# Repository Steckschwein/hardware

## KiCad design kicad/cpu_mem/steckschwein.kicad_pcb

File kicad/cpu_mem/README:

OBSOLETE

This is the old CPU/memory board without RDY-generator.
It has been superseded by ../cpu_mem_rdy

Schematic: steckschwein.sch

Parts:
C1, C5, C6, C7, C8, C9, C10: 100n; C1
C2: 10n; C1
C3: 1n; C1
C4: 1µ; Elko_vert_DM5_RM2-5
C16: CP2; Elko_vert_11.2x7.5mm_RM2.5
D1, D2, D3: LED; LED-3MM
P1: CONN_02X04; Pin_Header_Straight_2x04
P3: CONN_01X03; Pin_Header_Straight_1x03
P4: CONN_02X02; Pin_Header_Straight_2x02
P6: POWER; Pin_Header_Angled_1x04
R1, R2, R3, R4: 3.3k; R3
R5, R6: 1M; R3
R7, R8, R9: 270; R3
SW1: SW_PUSH; PUSH_BUTT_SHAPE1
U1: W65C02SP; DIP-40__600_ELL
U2: LM555N; DIP-8__300_ELL
U3: 74HCT00; DIP-14__300_ELL
U4: 74LS393; DIP-14__300_ELL
U6: 28C256; DIP-28__600_ELL
U7, U8: HM62256BLP-7; DIP-28__600_ELL
X1: OSC; OSCILLATOR_KXO-200_LargePads

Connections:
/Connector/A0: U1.9 (A0), U6.10 (A0), U7.10 (A0), U8.10 (A0); also elsewhere on the board
/Connector/A1: U1.10 (A1), U6.9 (A1), U7.9 (A1), U8.9 (A1); also elsewhere on the board
/Connector/A2: U1.11 (A2), U6.8 (A2), U7.8 (A2), U8.8 (A2); also elsewhere on the board
/Connector/A3: U1.12 (A3), U6.7 (A3), U7.7 (A3), U8.7 (A3); also elsewhere on the board
/Connector/A4: U1.13 (A4), U6.6 (A4), U7.6 (A4), U8.6 (A4); also elsewhere on the board
/Connector/A5: U1.14 (A5), U6.5 (A5), U7.5 (A5), U8.5 (A5); also elsewhere on the board
/Connector/D0: U1.33 (D0), U6.11 (D0), U7.11 (D0), U8.11 (D0); also elsewhere on the board
/Connector/D1: U1.32 (D1), U6.12 (D1), U7.12 (D1), U8.12 (D1); also elsewhere on the board
/Connector/D2: U1.31 (D2), U6.13 (D2), U7.13 (D2), U8.13 (D2); also elsewhere on the board
/Connector/D3: U1.30 (D3), U6.15 (D3), U7.15 (D3), U8.15 (D3); also elsewhere on the board
/Connector/D4: U1.29 (D4), U6.16 (D4), U7.16 (D4), U8.16 (D4); also elsewhere on the board
/Connector/D5: U1.28 (D5), U6.17 (D5), U7.17 (D5), U8.17 (D5); also elsewhere on the board
/Connector/D6: U1.27 (D6), U6.18 (D6), U7.18 (D6), U8.18 (D6); also elsewhere on the board
/Connector/D7: U1.26 (D7), U6.19 (D7), U7.19 (D7), U8.19 (D7); also elsewhere on the board
/Connector/RESET_TRIG: C2.1, R5.2, SW1.1, U2.2 (TR); also elsewhere on the board
/IRQ: R1.1, U1.4 (IRQB); also elsewhere on the board
/NMI: R2.1, U1.6 (NMIB); also elsewhere on the board
/OE: U3.6, U6.22 (OE), U7.22 (~OE), U8.22 (~OE); also elsewhere on the board
/RESET: U1.40 (RESB), U3.11; also elsewhere on the board
/RW: U1.34 (R/WB), U3.1, U3.2, U3.4; also elsewhere on the board
/WE: U3.8, U7.27 (~WE), U8.27 (~WE); also elsewhere on the board
/decoder//CS_HIRAM: D3.2, U8.20 (~CS); also elsewhere on the board
/decoder//CS_LORAM: D2.2, U7.20 (~CS); also elsewhere on the board
/decoder//CS_ROM: D1.2, U6.20 (CS); also elsewhere on the board
/decoder/A6: U1.15 (A6), U6.4 (A6), U7.4 (A6), U8.4 (A6); also elsewhere on the board
/decoder/A7: U1.16 (A7), U6.3 (A7), U7.3 (A7), U8.3 (A7); also elsewhere on the board
/decoder/A8: U1.17 (A8), U6.25 (A8), U7.25 (A8), U8.25 (A8); also elsewhere on the board
/decoder/A9: U1.18 (A9), U6.24 (A9), U7.24 (A9), U8.24 (A9); also elsewhere on the board
/decoder/A10: U1.19 (A10), U6.21 (A10), U7.21 (A10), U8.21 (A10); also elsewhere on the board
/decoder/A11: U1.20 (A11), U6.23 (A11), U7.23 (A11), U8.23 (A11); also elsewhere on the board
/decoder/A12: U1.22 (A12), U6.2 (A12), U7.2 (A12), U8.2 (A12); also elsewhere on the board
/decoder/A13: U1.23 (A13), U7.26 (A13), U8.26 (A13); also elsewhere on the board
/decoder/A14: U1.24 (A14), U7.1 (A14), U8.1 (A14); also elsewhere on the board
/decoder/A15: U1.25 (A15); also elsewhere on the board
/decoder/BANK1: U6.26 (A13); also elsewhere on the board
/decoder/BANK2: U6.1 (A14); also elsewhere on the board
GND: C1.2, C2.2, C3.2, C4.2, C5.2, C6.2, C7.2, C8.2, C9.2, C10.2, C16.2, P4.4, P6.2, P6.3, SW1.2, U1.21 (VSS), U2.1 (GND), U3.7 (GND), U4.2 (Mr), U4.7 (GND), U4.12 (Mr), U4.13 (Cp), U6.14 (GND), U7.14 (GND), U8.14 (GND), X1.7 (GND); also elsewhere on the board
unnamed: C3.1, U2.5 (CV)
unnamed: C4.1, R6.1, U2.6 (THR), U2.7 (DIS)
unnamed: D1.1, R7.1
unnamed: D2.1, R8.1
unnamed: D3.1, R9.1
unnamed: P1.1, P1.3, P1.5, P1.7, P3.1, U1.37 (PH0-IN)
unnamed: P1.2, U4.3 (Q0)
unnamed: P1.4, U4.4 (Q1)
unnamed: P1.6, U4.5 (Q2)
unnamed: P1.8, U4.6 (Q3)
unnamed: P3.3, U1.39 (PHI2)
unnamed: P4.1, U1.36 (BE)
unnamed: P4.2, R4.2
unnamed: P4.3, U1.1 (VPB)
unnamed: U2.3 (Q), U3.12, U3.13
unnamed: U3.3, U3.10
unnamed: U4.1 (Cp), X1.8 (FREQ)
PHI2: P3.2, U3.5, U3.9; also elsewhere on the board
RDY: R3.1, U1.2 (RDY); also elsewhere on the board
VCC: C1.1, C5.1, C6.1, C7.1, C8.1, C9.1, C10.1, C16.1, P6.1, R1.2, R2.2, R3.2, R4.1, R5.1, R6.2, R7.2, R8.2, R9.2, U1.8 (VDD), U2.4 (R), U2.8 (VCC), U3.14 (VCC), U4.14 (VCC), U6.27 (WE), U6.28 (VCC), U7.28 (VCC), U8.28 (VCC), X1.14 (+5V); also elsewhere on the board

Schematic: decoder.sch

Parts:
C11, C12, C13: 100n; C1
D4, D5, D6, D7, D8, D9, D10, D11: LED; LED-3MM
P2: CONN_01X08; Pin_Header_Straight_1x08
R10, R11, R12, R13, R14, R15, R16, R17: 270; R3
U5: GAL22V10; DIP-24__300_ELL
U9: 74LS139; DIP-16__300_ELL
U11: 74LS273; DIP-20__300_ELL
U12: 74LS244; DIP-20__300_ELL

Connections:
/CS_IO0: U9.4 (O0); also elsewhere on the board
/CS_IO1: U9.5 (O1); also elsewhere on the board
/CS_IO2: U9.6 (O2); also elsewhere on the board
/CS_UART: U5.19 (I/O/Q); also elsewhere on the board
/CS_VDP: U5.21 (I/O/Q); also elsewhere on the board
/CS_VIA: U5.20 (I/O/Q); also elsewhere on the board
/Connector/A4: U5.13 (I), U9.2 (A0); also elsewhere on the board
/Connector/A5: U5.11 (I), U9.3 (A1); also elsewhere on the board
/Connector/D0: U11.3, U12.18; also elsewhere on the board
/Connector/D1: U11.4, U12.16; also elsewhere on the board
/Connector/D2: U11.7, U12.14; also elsewhere on the board
/Connector/D3: U11.8, U12.12; also elsewhere on the board
/Connector/D4: U11.13, U12.9; also elsewhere on the board
/Connector/D5: U11.14, U12.7; also elsewhere on the board
/Connector/D6: U11.17, U12.5; also elsewhere on the board
/Connector/D7: U11.18, U12.3; also elsewhere on the board
/RESET: U11.1; also elsewhere on the board
/RW: U5.14 (I/O/Q), U9.14 (A0); also elsewhere on the board
/decoder//CS_HIRAM: U5.18 (I/O/Q); also elsewhere on the board
/decoder//CS_LORAM: U5.17 (I/O/Q); also elsewhere on the board
/decoder//CS_ROM: U5.16 (I/O/Q); also elsewhere on the board
/decoder//ROMOFF: P2.1, R10.2, U5.15 (I/O/Q), U11.2, U12.2
/decoder/A6: U5.10 (I); also elsewhere on the board
/decoder/A7: U5.9 (I); also elsewhere on the board
/decoder/A8: U5.8 (I); also elsewhere on the board
/decoder/A9: U5.7 (I); also elsewhere on the board
/decoder/A10: U5.6 (I); also elsewhere on the board
/decoder/A11: U5.5 (I); also elsewhere on the board
/decoder/A12: U5.4 (I); also elsewhere on the board
/decoder/A13: U5.3 (I); also elsewhere on the board
/decoder/A14: U5.2 (I); also elsewhere on the board
/decoder/A15: U5.1 (I/CLK); also elsewhere on the board
/decoder/BANK1: P2.2, R11.2, U11.5, U12.4; also elsewhere on the board
/decoder/BANK2: P2.3, R12.2, U11.6, U12.6; also elsewhere on the board
GND: C11.2, C12.2, C13.2, D4.2, D5.2, D6.2, D7.2, D8.2, D9.2, D10.2, D11.2, U5.12 (GND), U9.8 (GND), U11.10, U12.10; also elsewhere on the board
unnamed: D4.1, R10.1
unnamed: D5.1, R11.1
unnamed: D6.1, R12.1
unnamed: D7.1, R13.1
unnamed: D8.1, R14.1
unnamed: D9.1, R15.1
unnamed: D10.1, R16.1
unnamed: D11.1, R17.1
unnamed: P2.4, R13.2, U11.9, U12.8
unnamed: P2.5, R14.2, U11.12, U12.11
unnamed: P2.6, R15.2, U11.15, U12.13
unnamed: P2.7, R16.2, U11.16, U12.15
unnamed: P2.8, R17.2, U11.19, U12.17
unnamed: U5.22 (I/O/Q), U9.15 (E)
unnamed: U5.23 (I/O/Q), U9.1 (E)
unnamed: U9.12 (O0), U11.11
unnamed: U9.9 (O3), U12.1, U12.19
PHI2: U9.13 (A1); also elsewhere on the board
VCC: C11.1, C12.1, C13.1, U5.24 (VCC), U9.16 (VCC), U11.20, U12.20; also elsewhere on the board

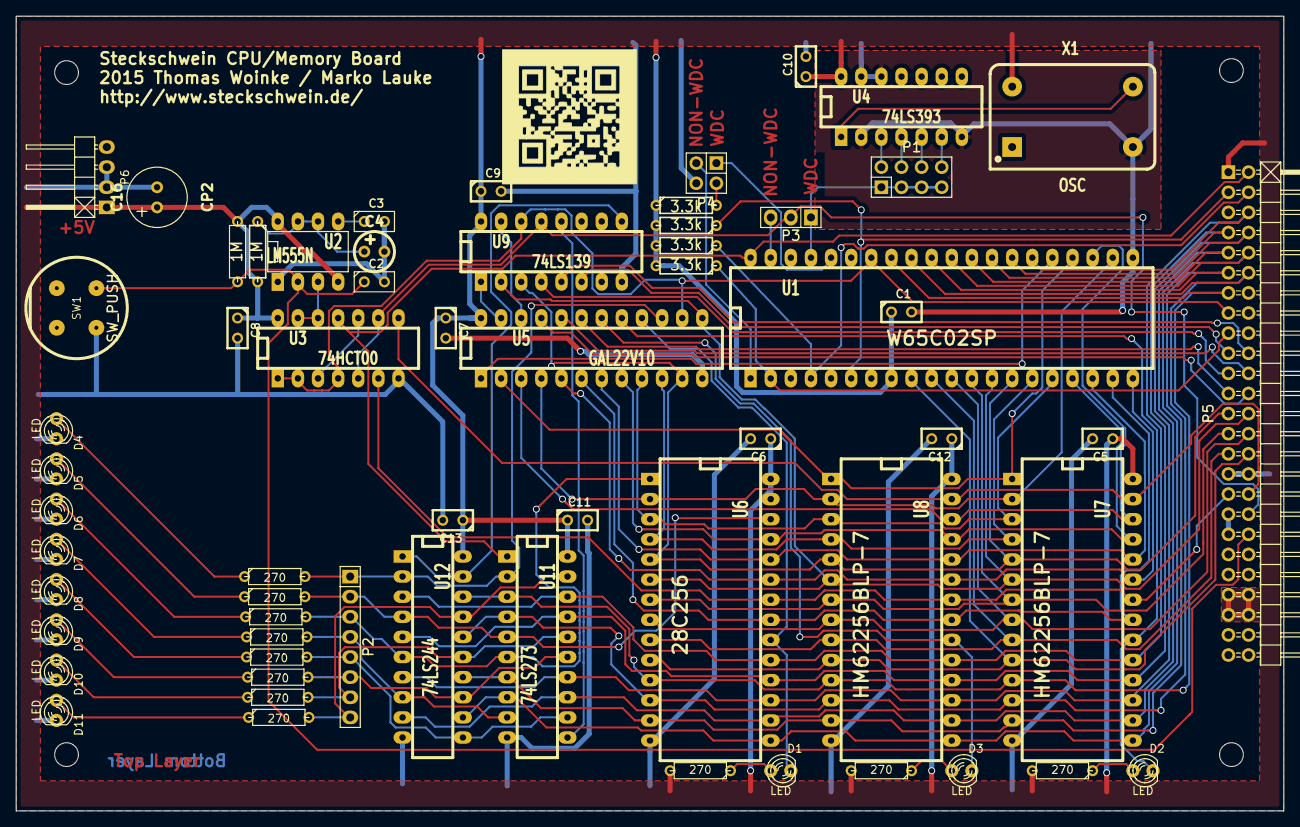
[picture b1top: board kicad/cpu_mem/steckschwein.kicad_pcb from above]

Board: 2 copper layers, 160.0 x 100.3 mm, 65 parts (0 on the bottom side), 81 nets.

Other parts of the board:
MH1, MH2, MH3, MH4: MountingHole_3mm_RevA_Date21Jun2010; MountingHole_3mm
P5: CONN_02X25; Pin_Header_Angled_2x25

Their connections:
/CS_IO0: P5.21; also elsewhere on the board
/CS_IO1: P5.20; also elsewhere on the board
/CS_IO2: P5.19; also elsewhere on the board
/CS_UART: P5.23; also elsewhere on the board
/CS_VDP: P5.24; also elsewhere on the board
/CS_VIA: P5.22; also elsewhere on the board
/Connector/A0: P5.30; also elsewhere on the board
/Connector/A1: P5.29; also elsewhere on the board
/Connector/A2: P5.28; also elsewhere on the board
/Connector/A3: P5.27; also elsewhere on the board
/Connector/A4: P5.26; also elsewhere on the board
/Connector/A5: P5.25; also elsewhere on the board
/Connector/D0: P5.13; also elsewhere on the board
/Connector/D1: P5.12; also elsewhere on the board
/Connector/D2: P5.11; also elsewhere on the board
/Connector/D3: P5.10; also elsewhere on the board
/Connector/D4: P5.9; also elsewhere on the board
/Connector/D5: P5.8; also elsewhere on the board
/Connector/D6: P5.7; also elsewhere on the board
/Connector/D7: P5.6; also elsewhere on the board
/Connector/RESET_TRIG: P5.38; also elsewhere on the board
/IRQ: P5.4; also elsewhere on the board
/NMI: P5.3; also elsewhere on the board
/OE: P5.33; also elsewhere on the board
/RESET: P5.2; also elsewhere on the board
/RW: P5.15; also elsewhere on the board
/WE: P5.34; also elsewhere on the board
GND: P5.31, P5.32, P5.35, P5.37, P5.47, P5.48, P5.49, P5.50; also elsewhere on the board
PHI2: P5.36; also elsewhere on the board
RDY: P5.17; also elsewhere on the board
VCC: P5.1, P5.43, P5.44, P5.45, P5.46; also elsewhere on the board

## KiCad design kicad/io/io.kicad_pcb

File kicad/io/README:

OBSOLETE

This is the old I/O-board without integrated UART.
It has been superseded by ../io_uart

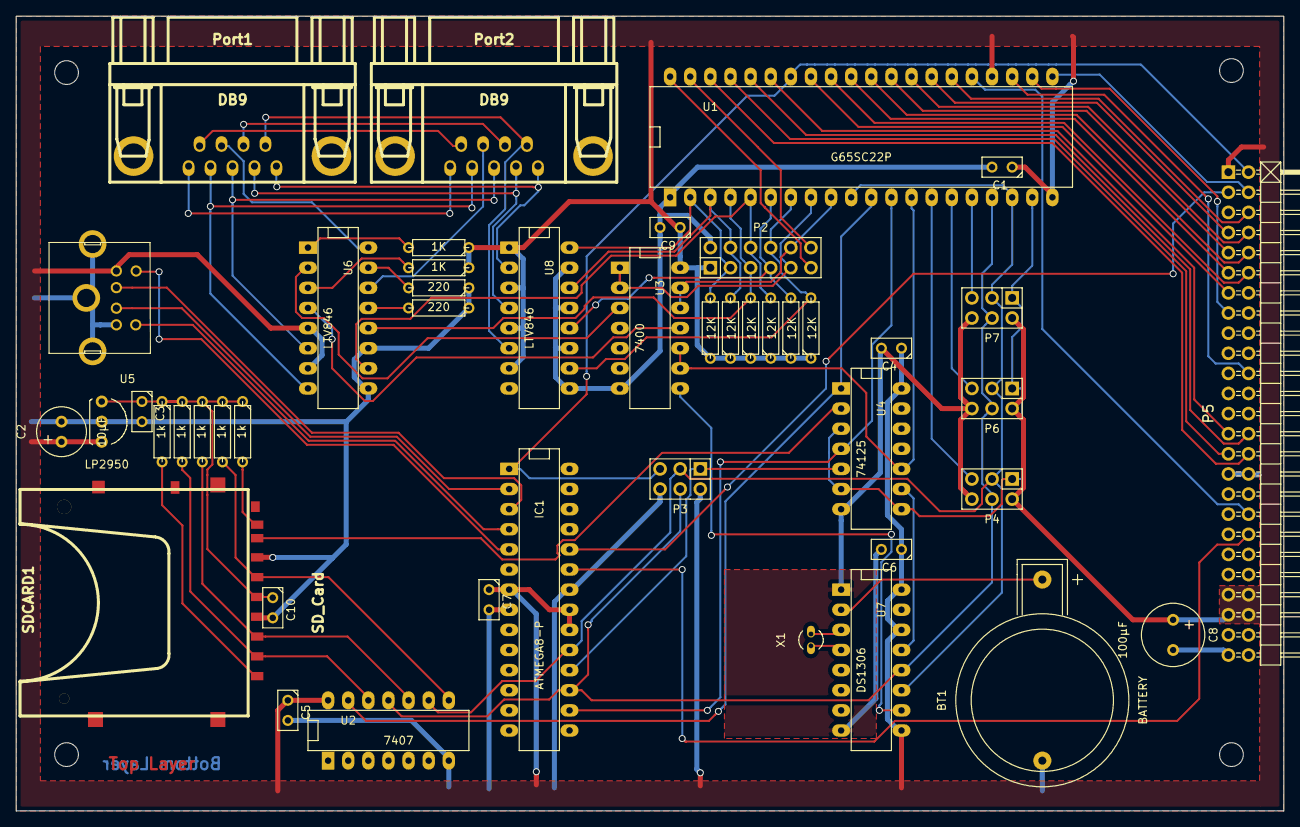
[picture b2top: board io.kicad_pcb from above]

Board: 2 copper layers, 160.0 x 100.3 mm, 50 parts (0 on the bottom side), 73 nets.

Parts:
BT1: BATTERY; CR2032H
C1, C3, C4, C5, C6, C7, C9, C10: 100nF; C1
C2: 10µF; Elko_vert_11.2x6.3mm_RM2.5
C8: 100µF; Elko_vert_11.5x8mm_RM3.5
IC1: ATMEGA8-P; DIP-28__300_ELL
MH1, MH2, MH3, MH4: MountingHole_3mm_RevA_Date21Jun2010; MountingHole_3mm
P1: PS/2 Keyboard; mini_din-M_DIN6
P2: CONN_02X06; Pin_Header_Straight_2x06
P3: ISP; Pin_Header_Straight_2x03
P4: SPI4; Pin_Header_Straight_2x03
P5: CONN_02X25; Pin_Header_Angled_2x25
P6: SPI5; Pin_Header_Straight_2x03
P7: SPI6; Pin_Header_Straight_2x03
Port1, Port2: DB9; DB_9M
R1, R2, R3, R4, R5: 1k; R3
R7, R8, R9, R10, R11, R12: 12K; R3
R13, R14: 220; R3
R15, R16: 1K; R3
SDCARD1: SD_Card; sd_socket
U1: G65SC22P; DIP-40__600_ELL
U2: 7407; DIP-14__300_ELL
U3: 7400; DIP-14__300_ELL
U4: 74125; DIP-14__300_ELL
U5: LP2950; TO-92-Free-inline-wide
U6, U8: LTV846; DIP-16__300_ELL
U7: DS1306; DIP-16__300_ELL
X1: CRYSTAL_SMD; Crystal_Round_Vertical_3mm_BigPad

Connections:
/CA1: P2.11, U1.40
/CA2: P2.12, U1.39
/CS_VIA: P5.22, U1.23
/Connector/A0: P5.30, U1.38
/Connector/A1: P5.29, U1.37
/Connector/A2: P5.28, U1.36
/Connector/A3: P5.27, U1.35
/Connector/D0: P5.13, U1.33
/Connector/D1: P5.12, U1.32
/Connector/D2: P5.11, U1.31
/Connector/D3: P5.10, U1.30
/Connector/D4: P5.9, U1.29
/Connector/D5: P5.8, U1.28
/Connector/D6: P5.7, U1.27
/Connector/D7: P5.6, U1.26
/Connector/RESET_TRIG: IC1.23, P5.38
/IRQ: P5.4, U1.21
/Joystick Ports/J_Down: P2.4, R9.2, U1.3, U8.14
/Joystick Ports/J_Fire1: P2.7, R8.2, U1.6, U8.12
/Joystick Ports/J_Fire2: P2.8, R7.2, U1.7, U8.10
/Joystick Ports/J_Left: P2.5, R12.2, U1.4, U6.12
/Joystick Ports/J_Right: P2.6, R11.2, U1.5, U6.10
/Joystick Ports/J_Up: P2.3, R10.2, U1.2, U8.16
/Joystick Ports/PortSel01: P2.9, U1.8, U3.1, U3.2
/Joystick Ports/PortSel02: P2.10, U1.9, U3.12, U3.13
/NMI: IC1.24, P5.3
/RESET: IC1.1, P3.5, P5.2, U1.34
/RW: P5.15, U1.22
/SD Card/SPI_CLK: IC1.19, P3.3, P4.3, P6.3, P7.3, U1.10, U1.18, U2.9, U7.11
/SD Card/SPI_MISO: P4.1, P6.1, P7.1, U1.19, U4.3, U4.6, U4.8
/SD Card/SPI_MOSI: IC1.17, P3.4, P4.4, P6.4, P7.4, U1.17, U2.11, U7.12
/SD Card/SPI_SS1: U1.11, U2.13, U4.1
/~SPI_SS2: IC1.16, U1.12, U4.4
/~SPI_SS3: U1.13, U3.9, U3.10, U4.10
/~SPI_SS4: P4.5, U1.14
/~SPI_SS5: P6.5, U1.15
/~SPI_SS6: P7.5, U1.16
GND: BT1.2, C1.2, C2.2, C3.2, C4.2, C5.2, C6.2, C7.2, C8.2, C9.2, C10.2, IC1.8, IC1.22, P1.3, P1.SH1, P1.SH2, P1.SH3, P2.2, P3.6, P4.6, P5.31, P5.32, P5.35, P5.37, P5.47, P5.48, P5.49, P5.50, P6.6, P7.6, R13.1, R14.1, SDCARD1.3, SDCARD1.6, U1.1, U2.7, U3.7, U4.7, U5.2, U6.9, U6.11, U7.1, U7.8, U8.9, U8.11, U8.13, U8.15
unnamed: BT1.1, U7.2
unnamed: C3.1, C10.1, R1.1, R2.1, R3.1, R4.1, R5.1, SDCARD1.4, U5.1
unnamed: IC1.2, P1.1
unnamed: IC1.3, P1.2
unnamed: IC1.4, P1.6
unnamed: IC1.5, P1.8
unnamed: IC1.18, P3.1, U4.5
unnamed: Port1.1, Port2.1, U8.2
unnamed: Port1.2, Port2.2, U8.4
unnamed: Port1.3, Port2.3, U6.6
unnamed: Port1.4, Port2.4, U6.8
unnamed: Port1.5, Port2.5
unnamed: Port1.6, Port2.6, U8.6
unnamed: Port1.7, Port2.7
unnamed: Port1.8, U6.16
unnamed: Port1.9, Port2.9
unnamed: Port2.8, U6.14
unnamed: R1.2, SDCARD1.5, U2.8
unnamed: R2.2, SDCARD1.2, U2.10
unnamed: R3.2, SDCARD1.1, U2.12
unnamed: R4.2, SDCARD1.9
unnamed: R5.2, SDCARD1.8
unnamed: R13.2, U6.15
unnamed: R14.2, U6.13
unnamed: R15.2, U6.1
unnamed: R16.2, U6.3
unnamed: SDCARD1.7, U4.2
unnamed: U3.3, U6.2
unnamed: U3.8, U7.10
unnamed: U3.11, U6.4
unnamed: U4.9, U7.13
unnamed: U7.3, X1.2
unnamed: U7.4, X1.1
PHI2: P5.36, U1.25
VCC: C1.1, C2.1, C4.1, C5.1, C6.1, C7.1, C8.1, C9.1, IC1.7, IC1.20, IC1.21, P1.5, P2.1, P3.2, P4.2, P5.1, P5.43, P5.44, P5.45, P5.46, P6.2, P7.2, R7.1, R8.1, R9.1, R10.1, R11.1, R12.1, R15.1, R16.1, U1.20, U1.24, U2.14, U3.14, U4.14, U5.3, U6.5, U6.7, U7.9, U7.14, U7.16, U8.1, U8.3, U8.5, U8.7

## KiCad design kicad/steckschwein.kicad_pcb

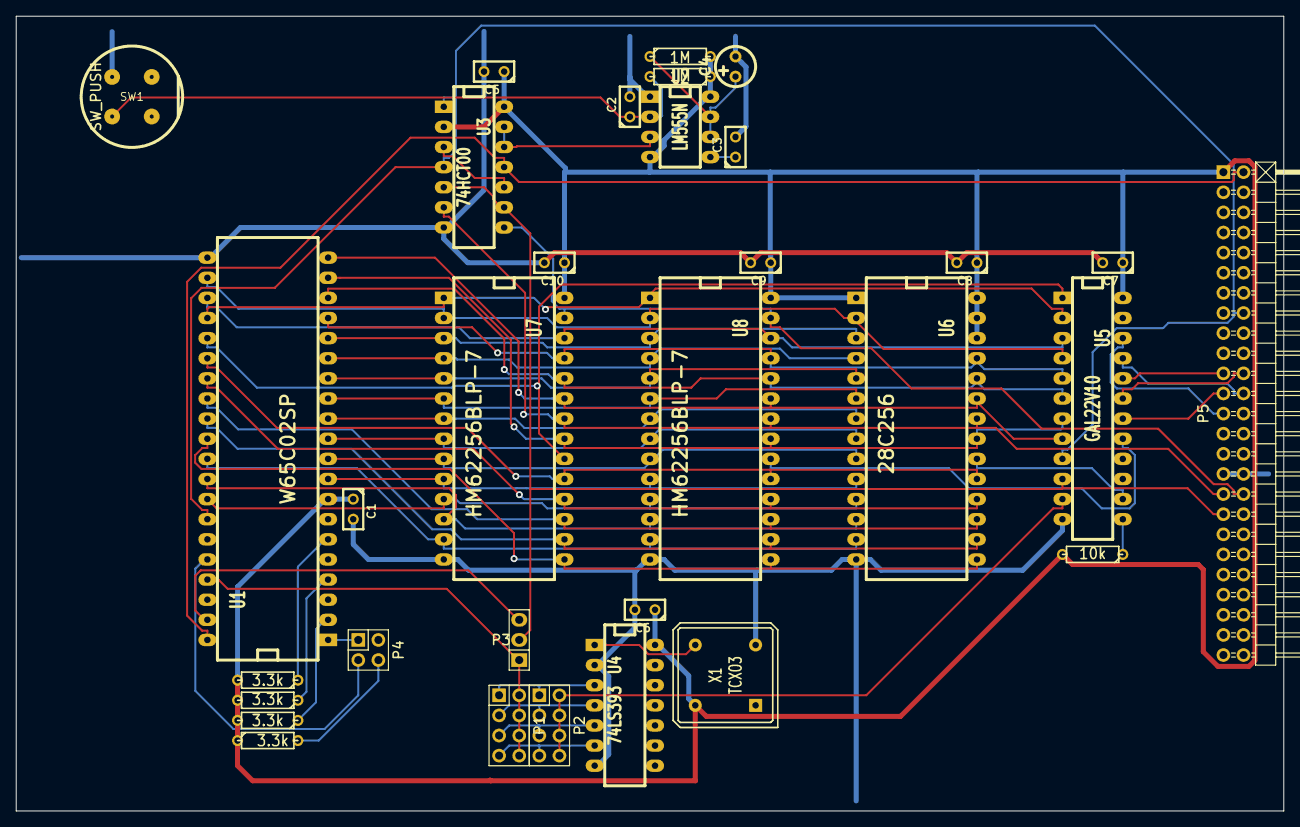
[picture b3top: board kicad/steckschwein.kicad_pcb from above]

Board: 2 copper layers, 160.0 x 100.3 mm, 32 parts (0 on the bottom side), 58 nets.

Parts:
C1, C5, C6, C7, C8, C9, C10: 100n; C1
C2: 10n; C1
C3: 1n; C1
C4: 1µ; Elko_vert_DM5_RM2-5
P1, P2: CONN_02X04; Pin_Header_Straight_2x04
P3: CONN_01X03; Pin_Header_Straight_1x03
P4: CONN_02X02; Pin_Header_Straight_2x02
P5: CONN_02X25; Pin_Header_Angled_2x25
R1, R2, R3, R4: 3.3k; R3
R5, R6: 1M; R3
R8: 10k; R3
SW1: SW_PUSH; PUSH_BUTT_SHAPE1
U1: W65C02SP; DIP-40__600_ELL
U2: LM555N; DIP-8__300_ELL
U3: 74HCT00; DIP-14__300_ELL
U4: 74LS393; DIP-14__300_ELL
U5: GAL22V10; DIP-24__300_ELL
U6: 28C256; DIP-28__600_ELL
U7, U8: HM62256BLP-7; DIP-28__600_ELL
X1: TCXO3; OSC_DIP8

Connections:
/A0: U1.9, U6.10, U7.10, U8.10
/A1: U1.10, U6.9, U7.9, U8.9
/A2: U1.11, U6.8, U7.8, U8.8
/A3: U1.12, U6.7, U7.7, U8.7
/A4: U1.13, U6.6, U7.6, U8.6
/A5: U1.14, U6.5, U7.5, U8.5
/A6: U1.15, U6.4, U7.4, U8.4
/A7: U1.16, U6.3, U7.3, U8.3
/A8: U1.17, U5.5, U6.25, U7.25, U8.25
/A9: U1.18, U5.6, U6.24, U7.24, U8.24
/A10: U1.19, U5.7, U6.21, U7.21, U8.21
/A11: U1.20, U5.8, U6.23, U7.23, U8.23
/A12: U1.22, U5.4, U6.2, U7.2, U8.2
/A13: U1.23, U5.3, U7.26, U8.26
/A14: U1.24, U5.2, U7.1, U8.1
/A15: U1.25, U5.1, U7.20
/CSR_VDP: P5.24, U5.21
/CSW_VDP: P5.25, U5.22
/CS_HIRAM: U5.17, U8.20
/CS_ROM: U5.14, U6.20
/CS_UART: P5.23, U5.18
/CS_VIA: P5.22, U5.19
/D0: U1.33, U6.11, U7.11, U8.11
/D1: U1.32, U6.12, U7.12, U8.12
/D2: U1.31, U6.13, U7.13, U8.13
/D3: U1.30, U6.15, U7.15, U8.15
/D4: U1.29, U6.16, U7.16, U8.16
/D5: U1.28, U6.17, U7.17, U8.17
/D6: U1.27, U6.18, U7.18, U8.18
/D7: U1.26, U6.19, U7.19, U8.19
/OE: P5.33, U3.6, U6.22, U7.22, U8.22
/RESET: P5.2, U1.40, U3.11
/ROMOFF: R8.1, U5.13
/RW: P5.16, U1.34, U3.1, U3.4, U5.9
/WE: P5.34, U3.8, U7.27, U8.27
CLK1: P2.2, P2.4, P2.6, P2.8, U5.11
E_LCD: P5.21, U5.20
GND: C1.2, C2.2, C3.2, C4.2, C5.2, C6.2, C7.2, C8.2, C9.2, C10.2, P4.2, P5.31, P5.32, SW1.2, U1.21, U2.1, U3.7, U4.2, U4.7, U5.12, U6.14, U7.14, U8.14, X1.4
unnamed: C2.1, R5.2, SW1.1, U2.2
unnamed: C3.1, U2.5
unnamed: C4.1, R6.1, U2.6, U2.7
unnamed: P1.1, P2.1, U4.3
unnamed: P1.3, P2.3, U4.4
unnamed: P1.5, P2.5, U4.5
unnamed: P1.7, P2.7, U4.6
unnamed: P3.3, U1.39
unnamed: P4.1, U1.1
unnamed: P4.3, U1.36
unnamed: P4.4, R4.2
unnamed: R1.1, U1.4
unnamed: R2.1, U1.6
unnamed: R3.1, U1.2
unnamed: U2.3, U3.12, U3.13
unnamed: U3.3, U3.10
unnamed: U4.1, X1.5
PH0-IN: P1.2, P1.4, P1.6, P1.8, P3.1, U1.37
PHI2: P3.2, P5.35, U3.5, U3.9, U5.10
VCC: C1.1, C5.1, C6.1, C7.1, C8.1, C9.1, C10.1, P5.1, R1.2, R2.2, R3.2, R4.1, R5.1, R6.2, R8.2, U1.8, U2.4, U2.8, U3.2, U3.14, U4.14, U5.24, U6.1, U6.26, U6.27, U6.28, U7.28, U8.28, X1.8

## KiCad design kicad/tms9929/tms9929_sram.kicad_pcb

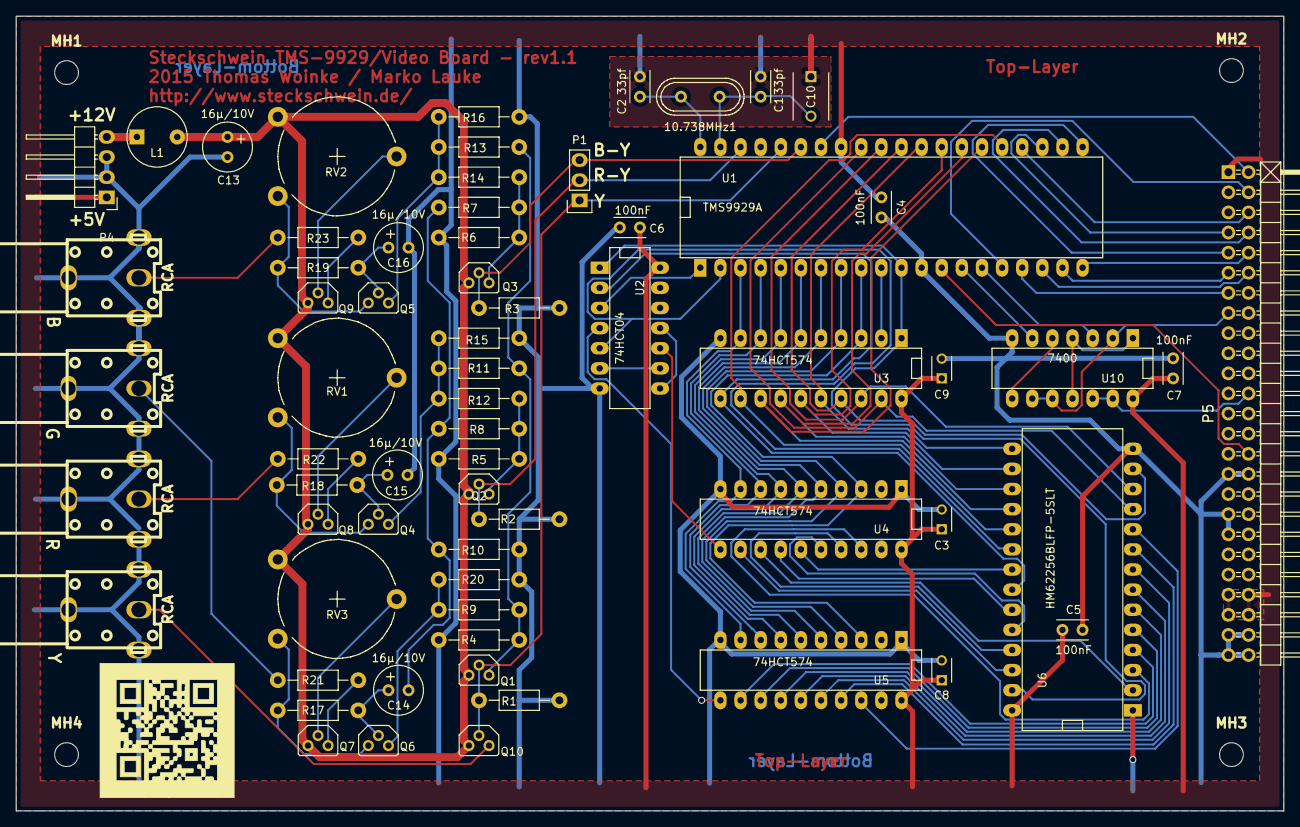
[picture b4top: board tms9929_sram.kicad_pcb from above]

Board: 2 copper layers, 160.0 x 100.3 mm, 70 parts (0 on the bottom side), 87 nets.

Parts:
10.738MHz1: CRYSTAL; Crystal_HC49-U_Vertical
Blue1: RCA; rca_black
C1, C2: 33pf; Capacitor4x3RM2.5
C3, C8, C9: 100nF; C_Disc_D3_P2.5
C4, C5, C6, C7: 100nF; Capacitor4x3RM2.5
C10: 5-50pf; C_Disc_D6_P5
C13, C14, C15, C16: 16µ/10V; Elko_vert_11.2x6.3mm_RM2.5
Green1: RCA; rca_black
L1: 47µH; INDUCTOR_V
MH1, MH2, MH3, MH4: MountingHole_3mm_RevA_Date21Jun2010; MountingHole_3mm
P1: CONN_01X03; Pin_Header_Straight_1x03
P4: Power; Pin_Header_Angled_1x04
P5: CONN_02X25; Pin_Header_Angled_2x25
Q1, Q2, Q3, Q4, Q5, Q6, Q7, Q8, Q9, Q10: BC550; TO92PN
R1, R2, R3: 470; Resistor_Horizontal_RM10mm
R4, R5, R6: 1K; Resistor_Horizontal_RM10mm
R7, R8, R9, R10, R11, R12, R13, R14, R15, R16, R20: 1K 1%; Resistor_Horizontal_RM10mm
R17, R18, R19: 100K; Resistor_Horizontal_RM10mm
R21, R22, R23: 100; Resistor_Horizontal_RM10mm
RV1, RV2, RV3: 5K; Potentiometer_Trimmer-Piher_PT15-V15_horizontal
Red1: RCA; rca_black
Sync1: RCA; rca_black
U1: TMS9929A; DIP-40__600_ELL
U2: 74HCT04; DIP-14__300_ELL
U3, U4, U5: 74HCT574; DIP-20__300_ELL
U6: HM62256BLFP-5SLT; DIP-28__600_ELL
U10: 7400; DIP-14__300_ELL

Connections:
+12V: L1.1, P4.4
/12VS: C13.1, L1.2, Q1.1, Q2.1, Q3.1, Q7.1, Q8.1, Q9.1, Q10.1, RV1.1, RV2.1, RV3.1
/50Pin/A0: P5.30, U1.13
/50Pin/D0: P5.13, U1.17
/50Pin/D1: P5.12, U1.18
/50Pin/D2: P5.11, U1.19
/50Pin/D3: P5.10, U1.20
/50Pin/D4: P5.9, U1.21
/50Pin/D5: P5.8, U1.22
/50Pin/D6: P5.7, U1.23
/50Pin/D7: P5.6, U1.24
/A0: U5.18, U6.10
/A1: U5.17, U6.9
/A2: U5.16, U6.8
/A3: U5.15, U6.7
/A4: U5.14, U6.6
/A5: U5.13, U6.5
/A6: U5.12, U6.4
/A7: U4.18, U6.3
/A8: U4.17, U6.25
/A9: U4.16, U6.24
/A10: U4.15, U6.21
/A11: U4.14, U6.23
/A12: U4.13, U6.2
/A13: U4.12, U6.26
/AD0: U1.10, U3.2
/AD1: U1.9, U3.3, U4.3, U5.3
/AD2: U1.8, U3.4, U4.4, U5.4
/AD3: U1.7, U3.5, U4.5, U5.5
/AD4: U1.6, U3.6, U4.6, U5.6
/AD5: U1.5, U3.7, U4.7, U5.7
/AD6: U1.4, U3.8, U4.8, U5.8
/AD7: U1.3, U3.9, U4.9, U5.9
/B-Y: P1.3, Q3.2, R3.1, U1.35
/CAS: U1.2, U2.5, U6.20
/COL: U2.10, U4.11
/CS_VDP: P5.24, U10.12, U10.13
/IRQ: P5.4, U1.16
/R-Y: P1.2, Q2.2, R2.1, U1.38
/RAS: U1.1, U2.3
/RD0: U1.32, U3.19, U6.11
/RD1: U1.31, U3.18, U6.12
/RD2: U1.30, U3.17, U6.13
/RD3: U1.29, U3.16, U6.15
/RD4: U1.28, U3.15, U6.16
/RD5: U1.27, U3.14, U6.17
/RD6: U1.26, U3.13, U6.18
/RD7: U1.25, U3.12, U6.19
/RESET: P5.2, U1.34
/RGB-B: Blue1.2, R23.1
/RGB-G: Green1.2, R21.1
/RGB-R: R22.1, Red1.2
/ROW: U2.4, U5.11
/RW: P5.15, U10.2, U10.9, U10.10
/SYNC: Q10.3, Sync1.2
/V_RW: U1.11, U2.1, U3.1, U6.27
/WR: U2.2, U3.11, U6.22
/Y: P1.1, Q1.2, Q10.2, R1.1, U1.36
GND: Blue1.1, C1.1, C2.1, C3.2, C4.2, C5.2, C6.2, C7.2, C8.2, C9.2, C10.1, C13.2, C15.2, C16.2, Green1.1, P4.2, P4.3, P5.31, P5.32, P5.35, P5.37, P5.47, P5.48, P5.49, P5.50, R1.2, R2.2, R3.2, R4.1, R5.1, R6.1, R10.1, R15.1, R16.1, R20.1, Red1.1, Sync1.1, U1.12, U2.7, U3.10, U4.1, U4.10, U5.1, U5.10, U6.1, U6.14, U10.7
unnamed: 10.738MHz1.1, C1.2, C10.2, U1.39
unnamed: 10.738MHz1.2, C2.2, U1.40
unnamed: C14.1, Q6.2, R17.2
unnamed: C14.2, R7.1, R8.1, R10.2
unnamed: C15.1, Q4.2, R18.1
unnamed: C16.1, Q5.2, R19.1
unnamed: Q1.3, R4.2, R9.2, R11.2, R13.2
unnamed: Q2.3, R5.2, R8.2, R12.2
unnamed: Q3.3, R6.2, R7.2, R14.2
unnamed: Q4.1, R18.2, RV1.3
unnamed: Q4.3, R11.1, R12.1, R15.2
unnamed: Q5.1, R19.2, RV2.3
unnamed: Q5.3, R13.1, R14.1, R16.2
unnamed: Q6.1, R17.1, RV3.3
unnamed: Q6.3, R9.1, R20.2
unnamed: Q7.2, RV3.2
unnamed: Q7.3, R21.2
unnamed: Q8.2, RV1.2
unnamed: Q8.3, R22.2
unnamed: Q9.2, RV2.2
unnamed: Q9.3, R23.2
unnamed: U1.14, U10.6
unnamed: U1.15, U10.3
unnamed: U2.6, U2.9
unnamed: U2.8, U2.11
unnamed: U10.1, U10.4, U10.11
unnamed: U10.5, U10.8
VCC: C3.1, C4.1, C5.1, C6.1, C7.1, C8.1, C9.1, P4.1, P5.1, P5.43, P5.44, P5.45, P5.46, U1.33, U2.14, U3.20, U4.20, U5.20, U6.28, U10.14
